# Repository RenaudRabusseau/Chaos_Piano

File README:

🎹 Chaos Piano: Phase 1 - Proximity Control Logic

📜 Project Overview

The Chaos Piano is an interactive, multi-sensory art installation designed for the Fondation du Doute. It transforms physical movement into an orchestration of light, sound, and vibration. This repository documents the evolution of the system from a bench prototype to a full-scale industrial control-command architecture.

The "Chaos" Logic
The system functions as an open-loop control-command system. Using an ultrasonic sensor, it monitors the distance of visitors. As a visitor approaches, the system increases the intensity and frequency of the feedback (LED strobing and auditory signals), creating a "chaotic" response that scales with proximity.

🛠 Current Technical State (Phase 1)
The project is currently in the Proof of Concept (PoC) stage, focusing on high-power switching and sensor data filtration.
1. Hardware Stack
Component               Industrial Role                 Specification
Microcontroller         Logic Unit (PLC equivalent)     Arduino Uno R3 (Atmega328P)
Sensor                  Data Acquisition                HC-SR04 (Ultrasonic)
Actuator                Power Output                    12V High-Brightness LED Strip
Power Interface         Output Stage                    IRLZ44N MOSFET (Logic Level)
Monitoring              Diagnostics                     Eventek ET580 Digital Multimeter

2. Power Architecture
To handle the 12V load while protecting the 5V microcontroller, the system utilizes a Common Ground architecture.
Logic Level Switching: An IRLZ44N MOSFET is used as a low-side switch, allowing the 5V Arduino pins to control the 12V power rail directly.
Signal Filtration: The code implements a Low-Pass Filter (Software Smoothing) to eliminate ultrasonic "noise" and ensure stable LED transitions.

🚀 Final Project Vision
The finished exhibit will scale this logic across a full-sized piano with the following expanded capabilities:
Haptic Feedback: Three 6V vibrating motors attached to the piano strings to create physical resonance.
Audio Manipulation: Piezoelectric microphones capturing raw string vibrations, processed through the Arduino with glitch, distortion, and flanger effects.
Advanced Processing: Transitioning to an RP2040-Zero (Dual-core ARM) to handle multi-threaded sensor acquisition and real-time audio processing.
Industrial Standards: Implementation of a Watchdog Timer for high availability and Opto-couplers for complete electrical isolation between power and logic stages.

📂 Repository Contents
/Code: Optimized C++ firmware for the proximity-to-strobe logic.
/Hardware: Wiring tables and schematics (Fritzing/Draw.io).
/Docs: Technical datasheets for the IRLZ44N and HC-SR04.

🎓 Academic Context
This project serves as a practical application of the Purdue Model (Levels 0 and 1). It demonstrates competency in:
Physical Interaction (Level 0): Interfacing sensors with a dynamic environment.
Control Logic (Level 1): Programming PWM modulation and interrupt-driven logic.
Hardware Safety: Implementing flyback protection (1N4007 diodes) for inductive motor loads.

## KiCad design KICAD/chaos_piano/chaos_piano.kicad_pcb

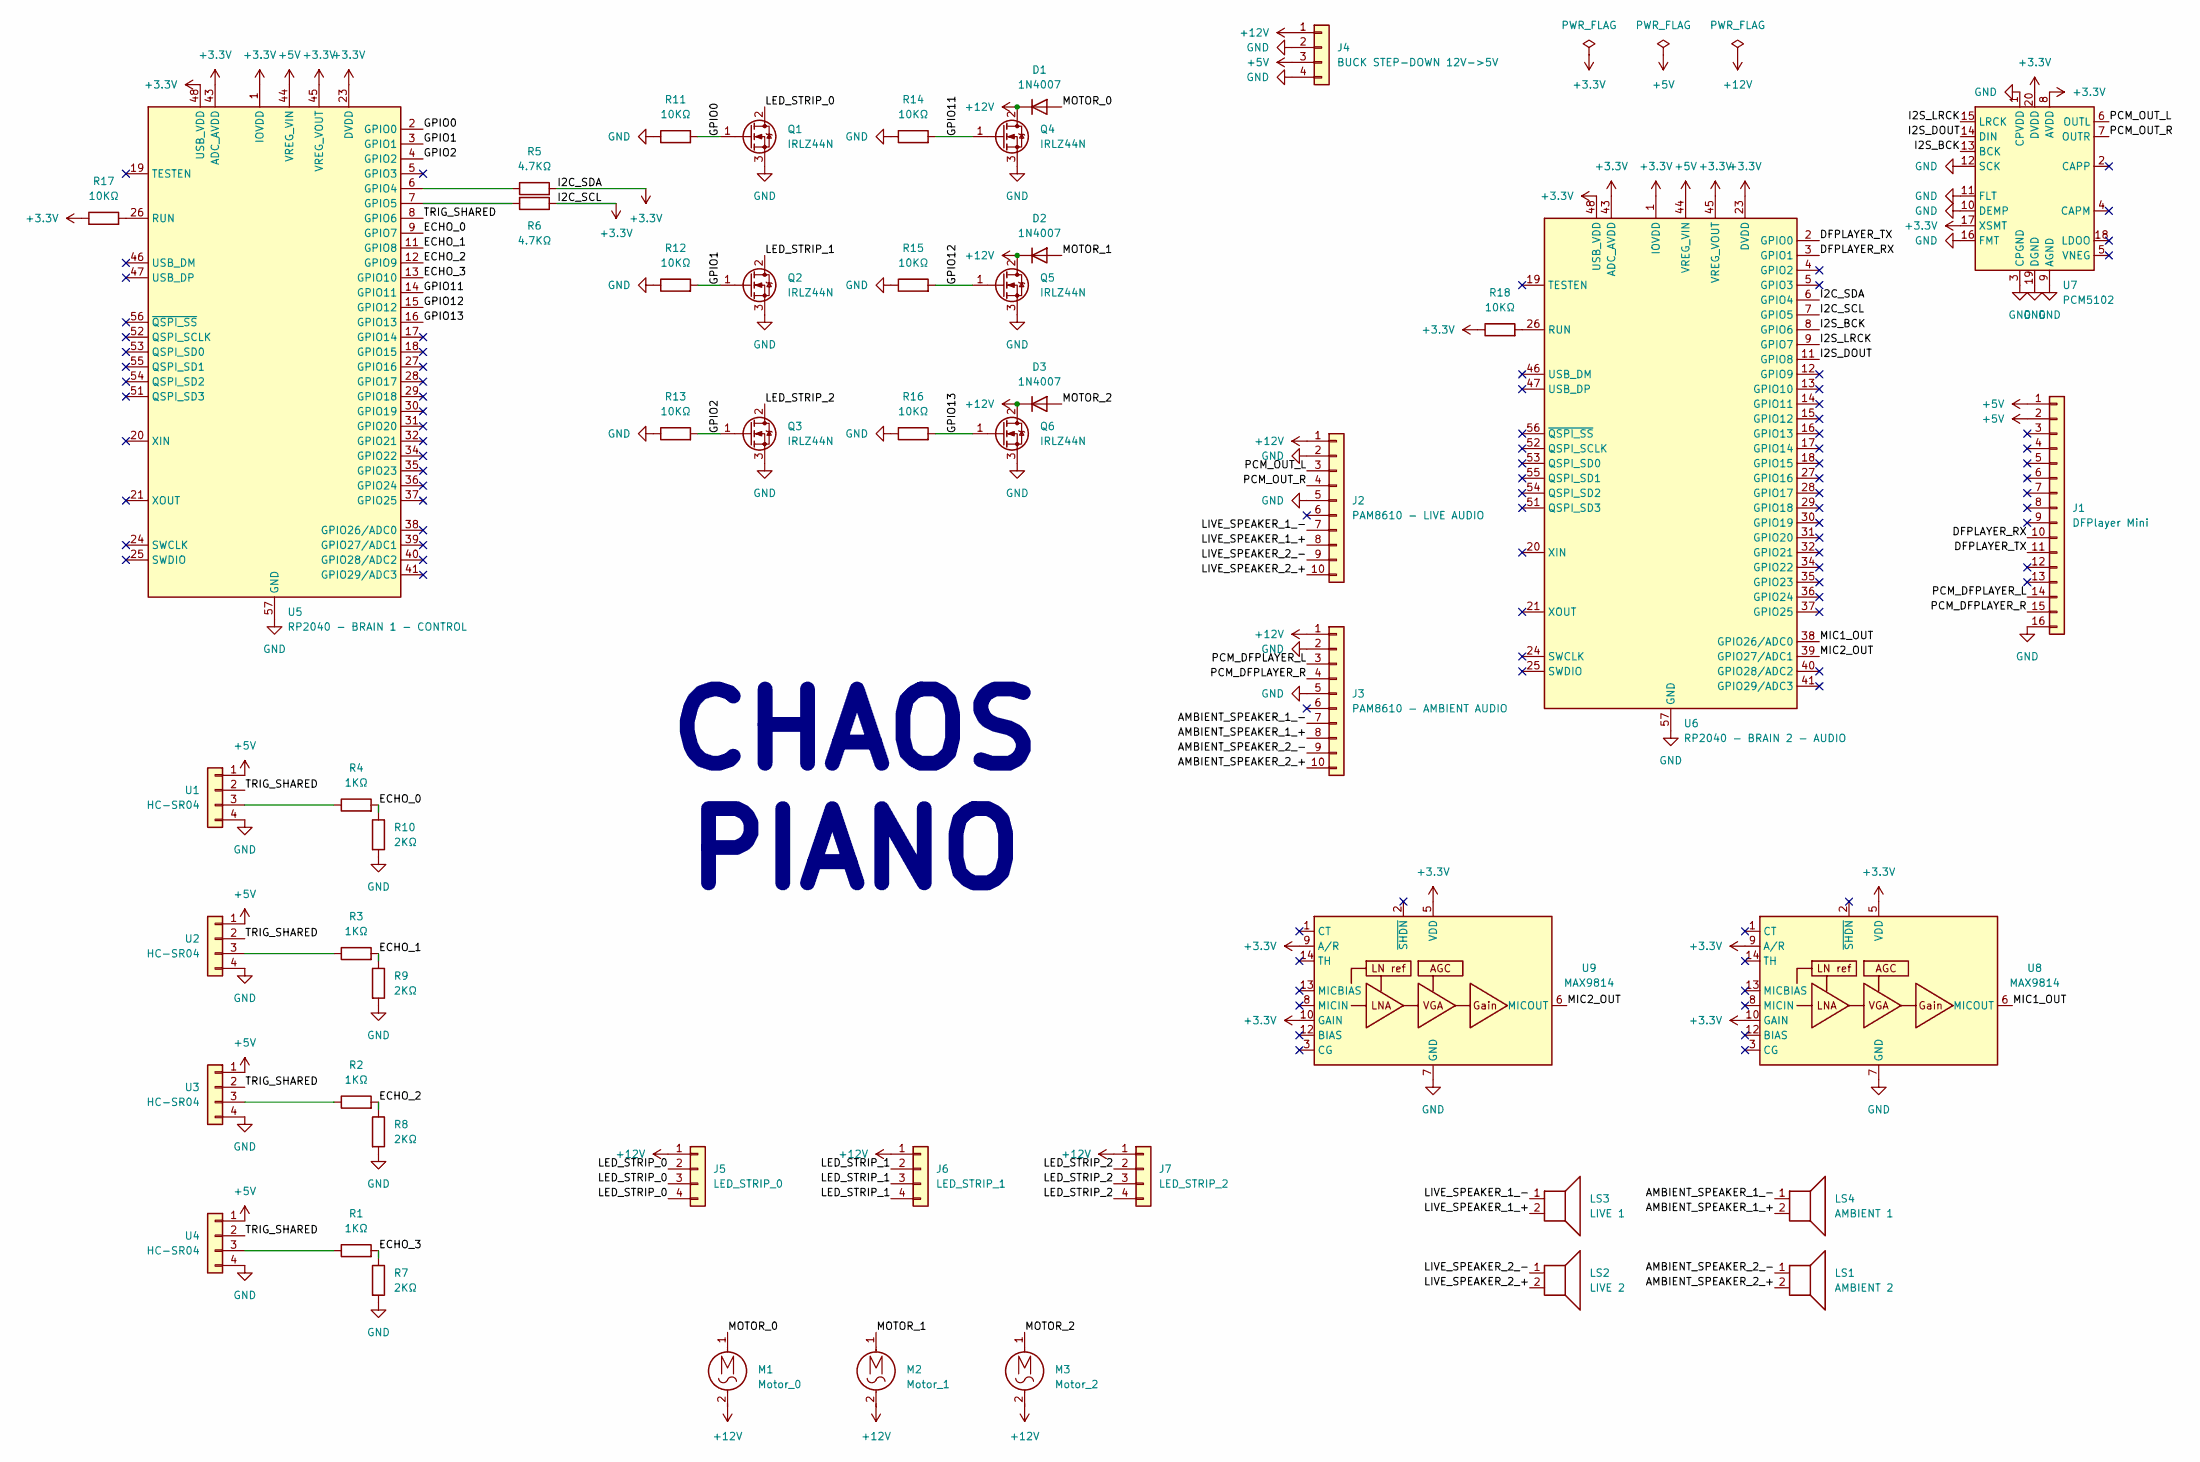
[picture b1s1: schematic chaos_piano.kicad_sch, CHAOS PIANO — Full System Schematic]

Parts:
D1, D2, D3: 1N4007; D_0201_0603Metric
J1: DFPlayer Mini; PinHeader_1x16_P2.54mm_Vertical
J2: PAM8610 - LIVE AUDIO; PinHeader_1x10_P2.54mm_Vertical
J3: PAM8610 - AMBIENT AUDIO; PinHeader_1x10_P2.54mm_Vertical
J4: BUCK STEP-DOWN 12V->5V; PinHeader_1x04_P2.54mm_Vertical
J5: LED_STRIP_0; PinHeader_1x04_P2.54mm_Vertical
J6: LED_STRIP_1; PinHeader_1x04_P2.54mm_Vertical
J7: LED_STRIP_2; PinHeader_1x04_P2.54mm_Vertical
LS1: AMBIENT 2; PinHeader_1x02_P2.54mm_Vertical
LS2: LIVE 2; PinHeader_1x02_P2.54mm_Vertical
LS3: LIVE 1; PinHeader_1x02_P2.54mm_Vertical
LS4: AMBIENT 1; PinHeader_1x02_P2.54mm_Vertical
M1: Motor_0; PinHeader_1x02_P2.54mm_Vertical
M2: Motor_1; PinHeader_1x02_P2.54mm_Vertical
M3: Motor_2; PinHeader_1x02_P2.54mm_Vertical
Q1, Q2, Q3, Q4, Q5, Q6: IRLZ44N; TO-220-3_Vertical
R1, R2, R3, R4: 1KΩ; R_0805_2012Metric
R5, R6: 4.7KΩ; R_0805_2012Metric
R7, R8, R9, R10: 2KΩ; R_0805_2012Metric
R11, R12, R13, R14, R15, R16, R17, R18: 10KΩ; R_0805_2012Metric
U1, U2, U3, U4: HC-SR04; PinHeader_1x04_P2.54mm_Vertical
U5: RP2040 - BRAIN 1 - CONTROL; QFN-56-1EP_7x7mm_P0.4mm_EP3.2x3.2mm
U6: RP2040 - BRAIN 2 - AUDIO; QFN-56-1EP_7x7mm_P0.4mm_EP3.2x3.2mm
U7: PCM5102; TSSOP-20_4.4x6.5mm_P0.65mm
U8, U9: MAX9814; DFN-14-1EP_3x3mm_P0.4mm_EP1.78x2.35mm

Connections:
+3.3V: R5.2, R6.1, R17.1, R18.1, U5.1 (IOVDD), U5.10 (IOVDD), U5.22 (IOVDD), U5.23 (DVDD), U5.33 (IOVDD), U5.42 (IOVDD), U5.43 (ADC_AVDD), U5.45 (VREG_VOUT), U5.48 (USB_VDD), U5.49 (IOVDD), U5.50 (DVDD), U6.1 (IOVDD), U6.6 (GPIO4), U6.7 (GPIO5), U6.10 (IOVDD), U6.22 (IOVDD), U6.23 (DVDD), U6.33 (IOVDD), U6.42 (IOVDD), U6.43 (ADC_AVDD), U6.45 (VREG_VOUT), U6.48 (USB_VDD), U6.49 (IOVDD), U6.50 (DVDD), U7.8 (AVDD), U7.17 (XSMT), U7.20 (DVDD), U8.5 (VDD), U8.9 (A/R), U8.10 (GAIN), U9.5 (VDD), U9.9 (A/R), U9.10 (GAIN)
+5V: J1.1, J1.2, J4.3, U1.1, U2.1, U3.1, U4.1, U5.44 (VREG_VIN), U6.44 (VREG_VIN)
+12V: D1.1 (K), D2.1 (K), D3.1 (K), J2.1, J3.1, J4.1, J5.1, J6.1, J7.1, M1.2, M2.2, M3.2, Q4.2 (D), Q5.2 (D), Q6.2 (D)
/AMBIENT_SPEAKER_1_+: J3.8, LS4.2
/AMBIENT_SPEAKER_1_-: J3.7, LS4.1
/AMBIENT_SPEAKER_2_+: J3.10, LS1.2
/AMBIENT_SPEAKER_2_-: J3.9, LS1.1
/DFPLAYER_RX: J1.10, U6.3 (GPIO1)
/DFPLAYER_TX: J1.11, U6.2 (GPIO0)
/ECHO_0: R4.2, R10.1, U5.9 (GPIO7)
/ECHO_1: R3.2, R9.1, U5.11 (GPIO8)
/ECHO_2: R2.2, R8.1, U5.12 (GPIO9)
/ECHO_3: R1.2, R7.1, U5.13 (GPIO10)
/GPIO0: Q1.1 (G), R11.2, U5.2 (GPIO0)
/GPIO1: Q2.1 (G), R12.2, U5.3 (GPIO1)
/GPIO2: Q3.1 (G), R13.2, U5.4 (GPIO2)
/GPIO11: Q4.1 (G), R14.2, U5.14 (GPIO11)
/GPIO12: Q5.1 (G), R15.2, U5.15 (GPIO12)
/GPIO13: Q6.1 (G), R16.2, U5.16 (GPIO13)
/I2S_BCK: U6.8 (GPIO6), U7.13 (BCK)
/I2S_DOUT: U6.11 (GPIO8), U7.14 (DIN)
/I2S_LRCK: U6.9 (GPIO7), U7.15 (LRCK)
/LED_STRIP_0: J5.2, J5.3, J5.4, Q1.2 (D)
/LED_STRIP_1: J6.2, J6.3, J6.4, Q2.2 (D)
/LED_STRIP_2: J7.2, J7.3, J7.4, Q3.2 (D)
/LIVE_SPEAKER_1_+: J2.8, LS3.2
/LIVE_SPEAKER_1_-: J2.7, LS3.1
/LIVE_SPEAKER_2_+: J2.10, LS2.2
/LIVE_SPEAKER_2_-: J2.9, LS2.1
/MIC1_OUT: U6.38 (GPIO26/ADC0), U8.6 (MICOUT)
/MIC2_OUT: U6.39 (GPIO27/ADC1), U9.6 (MICOUT)
/MOTOR_0: D1.2 (A), M1.1
/MOTOR_1: D2.2 (A), M2.1
/MOTOR_2: D3.2 (A), M3.1
/PCM_DFPLAYER_L: J1.14, J3.3
/PCM_DFPLAYER_R: J1.15, J3.4
/PCM_OUT_L: J2.3, U7.6 (OUTL)
/PCM_OUT_R: J2.4, U7.7 (OUTR)
/TRIG_SHARED: U1.2, U2.2, U3.2, U4.2, U5.8 (GPIO6)
GND: J1.16, J2.2, J2.5, J3.2, J3.5, J4.2, J4.4, Q1.3 (S), Q2.3 (S), Q3.3 (S), Q4.3 (S), Q5.3 (S), Q6.3 (S), R7.2, R8.2, R9.2, R10.2, R11.1, R12.1, R13.1, R14.1, R15.1, R16.1, U1.4, U2.4, U3.4, U4.4, U5.57 (GND), U6.57 (GND), U7.1 (CPVDD), U7.3 (CPGND), U7.9 (AGND), U7.10 (DEMP), U7.11 (FLT), U7.12 (SCK), U7.16 (FMT), U7.19 (DGND), U8.4 (GND), U8.7 (GND), U8.11 (GND), U8.15 (GND), U9.4 (GND), U9.7 (GND), U9.11 (GND), U9.15 (GND)
unnamed: R4.1, U1.3
unnamed: R3.1, U2.3
unnamed: R2.1, U3.3
unnamed: R1.1, U4.3
unnamed: R5.1, U5.6 (GPIO4)
unnamed: R6.2, U5.7 (GPIO5)
unnamed: R17.2, U5.26 (RUN)
unnamed: R18.2, U6.26 (RUN)

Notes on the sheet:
CHAOS PIANO

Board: 2 copper layers, 50 parts (0 on the bottom side), 48 nets, no tracks yet.

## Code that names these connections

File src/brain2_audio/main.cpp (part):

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// It plays audio from an SD card through its own analog outputs,
// which go to PAM8610 amplifier #2 (separate from the I2S audio path).

#define DFPLAYER_SERIAL Serial1  // UART0 on GPIO0 (TX) and GPIO1 (RX)

// Send a raw command frame to the DFPlayer.
// Frame format: 0x7E FF 06 CMD 00 PARAM_H PARAM_L CHECKSUM_H CHECKSUM_L 0xEF
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// zero jitter (unlike analogRead which has timing variations that sound
// like bitcrushing artifacts).

I2S i2sOutput(OUTPUT, PIN_I2S_BCK, PIN_I2S_DOUT);  // BCK=GPIO6, DOUT=GPIO8
ADCInput micInput(PIN_PIEZO_0, PIN_PIEZO_1);  // two channels, interleaved

// ---------------------------------------------------------------------------
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    // Initialize UART and send play commands during setup (before the
    // audio loop starts consuming CPU). The 1-second delay gives the
    // DFPlayer's own microcontroller time to boot after power-on.
    DFPLAYER_SERIAL.setTX(PIN_DFPLAYER_TX);
    DFPLAYER_SERIAL.setRX(PIN_DFPLAYER_RX);
    DFPLAYER_SERIAL.begin(9600);
    delay(1000);                         // DFPlayer boot time
    dfplayerSetVolume(DFPLAYER_VOL_MIN);
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
        // === MIC PATH ===
        // 1. Read both DMA samples (interleaved: mic0 then mic1) and remove DC bias
        int16_t raw0 = micInput.read();             // Mic 0 (GPIO26) - 12-bit ADC value
        int16_t raw1 = micInput.read();             // Mic 1 (GPIO27) - 12-bit ADC value
        int16_t mic0 = (raw0 - MIC_BIAS) * 2;      // Center around zero
        int16_t mic1 = (raw1 - MIC_BIAS) * 2;      // Center around zero
        // Sum both mics and halve to prevent clipping (average = mono downmix)
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
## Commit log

2026-02-13 Repo initialization. Code, phase 1 doc and hardware schematics
2026-03-02 v0.2: Audio chain validation — DFPlayer + MAX9814 piezo + DSP effects
2026-04-07 Final desk prototype - dual PSU, dual mics, chaotic actuation
2026-04-07 Enhance README with project details and architecture
    Expanded project overview and technical details for the Chaos Piano installation, including system architecture, hardware components, audio processing, and academic context.
2026-04-07 Remove obsolete folder structure
